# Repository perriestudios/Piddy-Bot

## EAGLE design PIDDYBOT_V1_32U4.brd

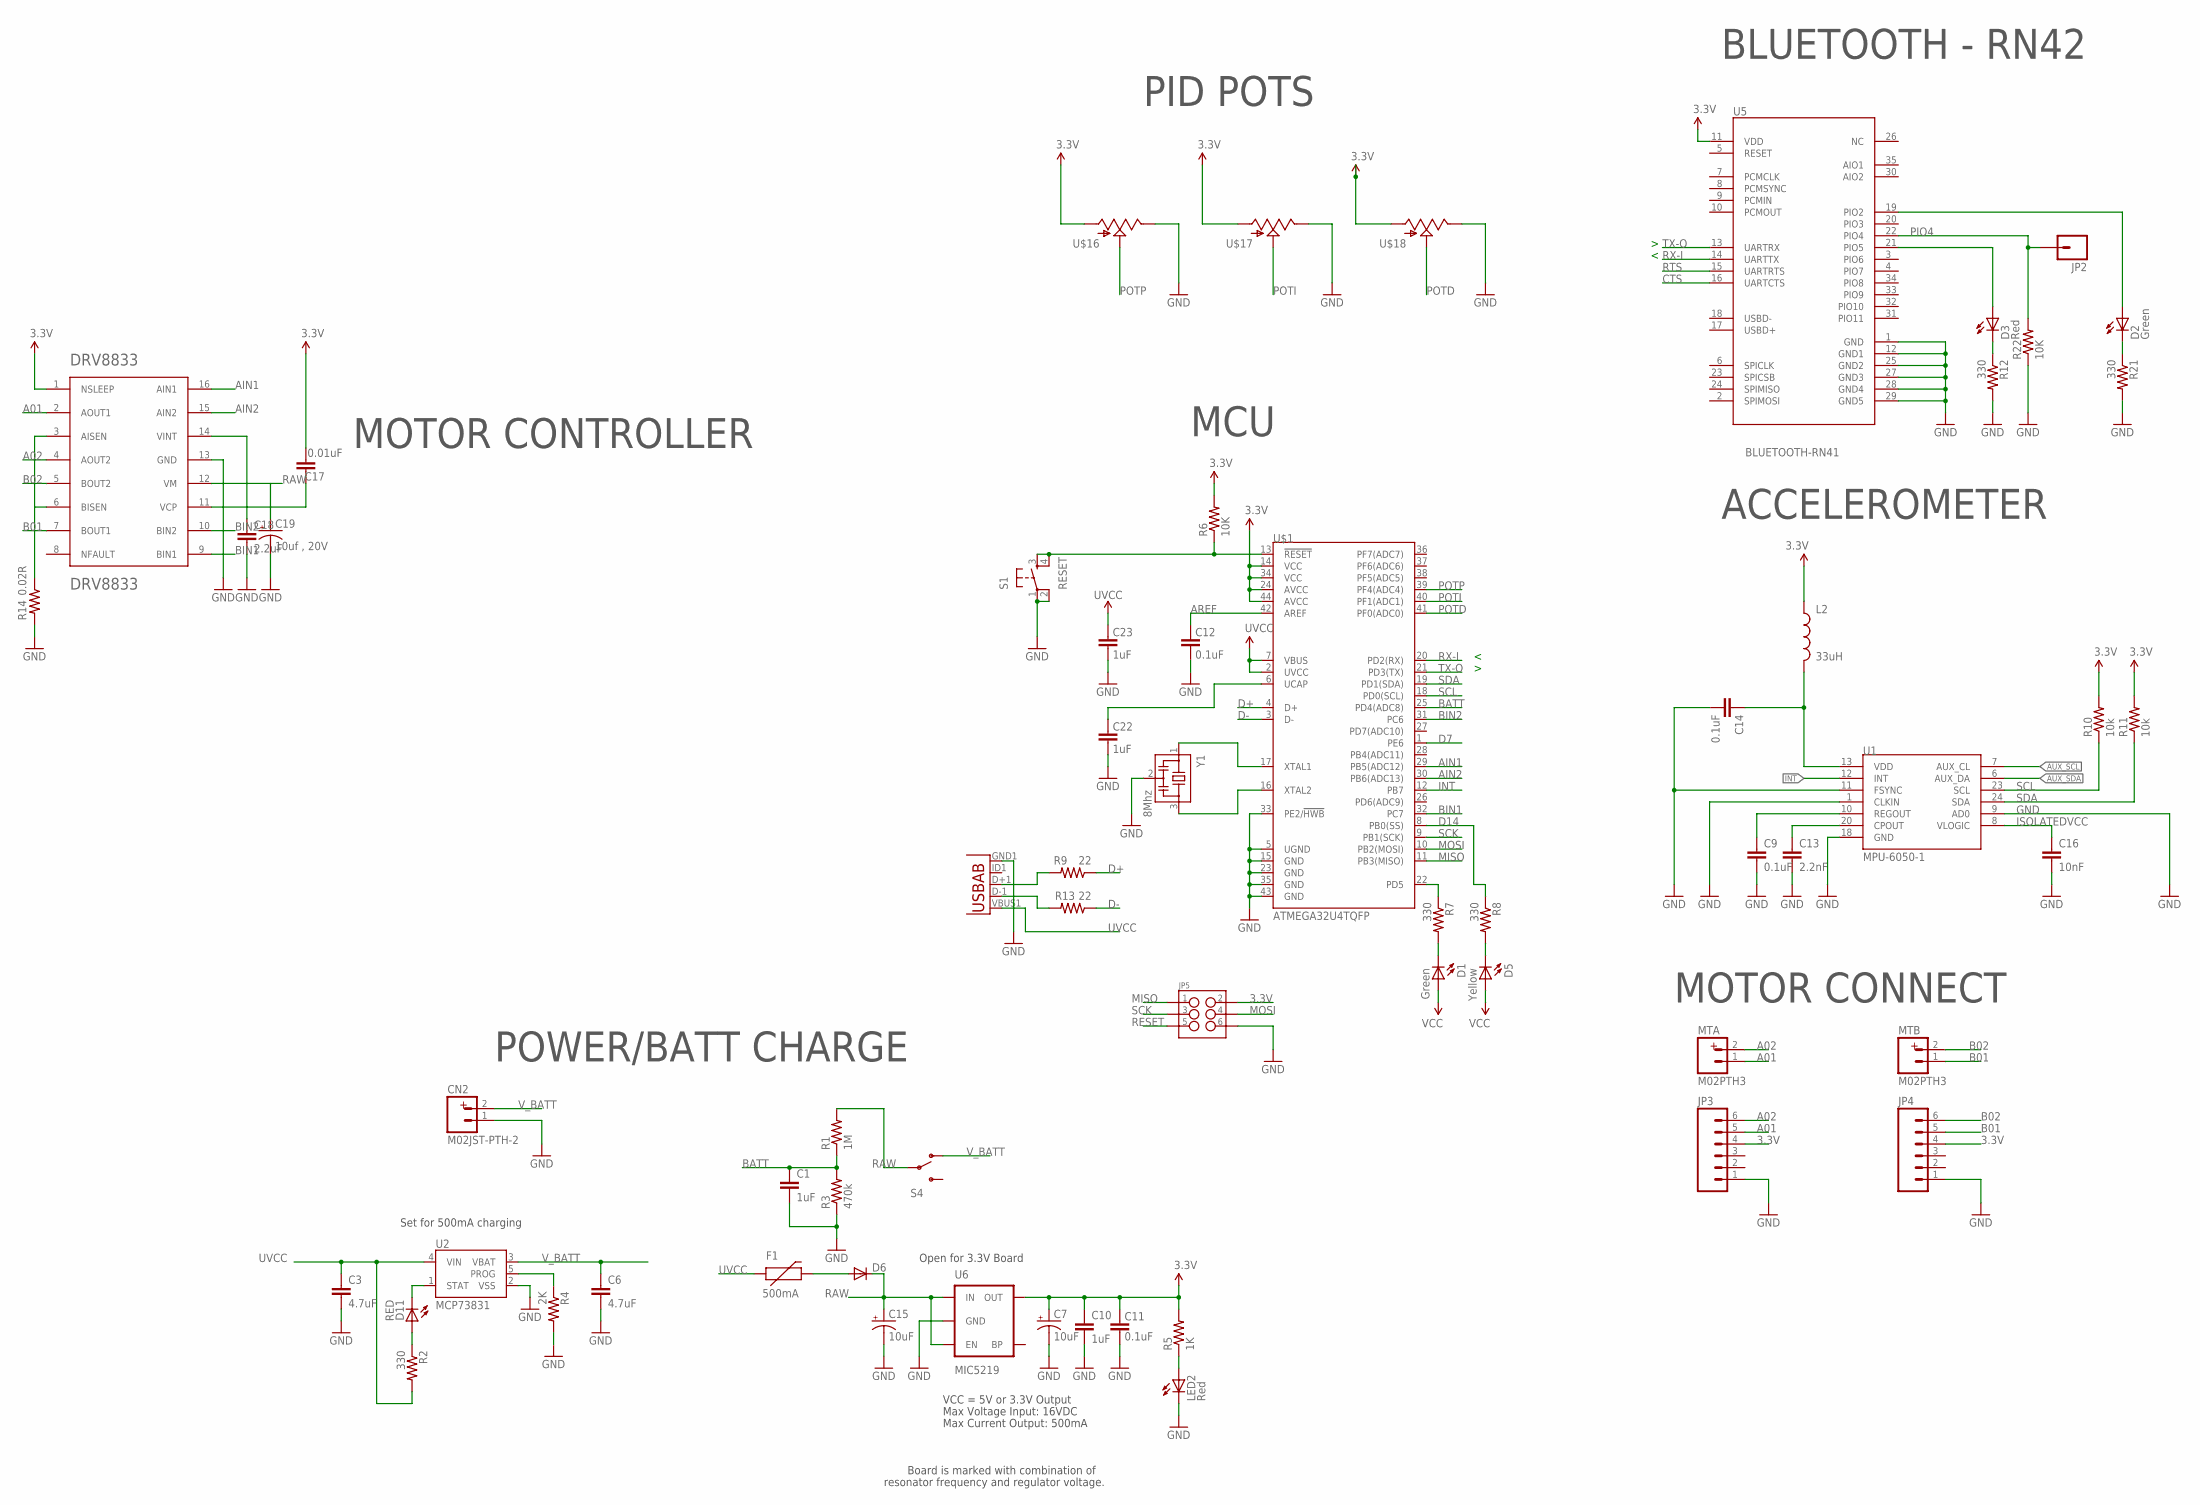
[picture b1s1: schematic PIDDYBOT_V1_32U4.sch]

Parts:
C1, C10, C22, C23: 1uF; 0603-CAP
C3, C6: 4.7uF; 0603-CAP
C7, C15: 10uF; EIA3216
C9, C11, C12, C14: 0.1uF; 0603-CAP
C13: 2.2nF; 0603-CAP
C16: 10nF; 0603-CAP
C17: 0.01uF; 0603-CAP
C18: 2.2uF; 0603-CAP
C19: 10uf , 20V; EIA3528
CN2: M02JST-PTH-2; JST-2-PTH
D1, D2: Green; LED-0603
D3: Red; LED-0603
D5: Yellow; LED-0603
D6: DIODESOD; SOD-323
D11: RED; LED-0603
DRV8833PWP1: DRV8833; SOP65P640X120-17N
F1: 500mA; PTC-1206
JP2: M01SMDNS; 1X01NS
JP3, JP4: M06SMD-1MM; 1X06-1MM
JP5: M03X2NO_SILK; 2X3-NS
L2: 33uH; C0402
LED2: Red; LED-0603
MTA: M02PTH3; 1X02_LONGPADS
MTB: M02PTH3; 1X02_LONGPADS
R1: 1M; 0603-RES
R2, R7, R8, R12, R21: 330; 0603-RES
R3: 470k; 0603-RES
R4: 2K; 0603-RES
R5: 1K; 0603-RES
R6, R22: 10K; 0603-RES
R9, R13: 22; 0603-RES
R10, R11: 10k; 0603-RES
R14: 0.02R; 0603-RES
S1: RESET; TACTILE_SWITCH_SMD
S4: SWITCH-SPDTPTH; SWITCH-SPDT
U1: MPU-6050-1; QFN-24-4MM2
U2: MCP73831; SOT23-5
U5: BLUETOOTH-RN41; RN41
U6: MIC5219; SOT23-5
U$1: ATMEGA32U4TQFP; SPARKFUN-DIGITALIC_TQFP44
U$16, U$17, U$18: POT; ALPS_POT
X2: USB-ABIN&OUT; USB-AB-MICRO-SMD-V03-IN&OUT
Y1: 8Mhz; CSTCR6M

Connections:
3.3V: C7.A (+), C10.1, C11.2, C17.2, D1.A, D5.A, DRV8833PWP1.1 (NSLEEP), JP3.4, JP4.4, JP5.2, L2.1, R5.2, R6.2, R10.2, R11.2, U5.11 (VDD), U6.5 (OUT), U$1.14 (VCC), U$1.24 (AVCC), U$1.34 (VCC), U$1.44 (AVCC), U$16.P$3 (A), U$17.P$3 (A), U$18.P$3 (A)
A01: DRV8833PWP1.2 (AOUT1), JP3.5, MTA.1
A02: DRV8833PWP1.4 (AOUT2), JP3.6, MTA.2
AIN1: DRV8833PWP1.16 (AIN1), U$1.29 (PB5(ADC12))
AIN2: DRV8833PWP1.15 (AIN2), U$1.30 (PB6(ADC13))
AREF: C12.2, U$1.42 (AREF)
AUX_SCL: U1.7 (AUX_CL)
AUX_SDA: U1.6 (AUX_DA)
B01: DRV8833PWP1.7 (BOUT1), JP4.5, MTB.1
B02: DRV8833PWP1.5 (BOUT2), JP4.6, MTB.2
BATT: C1.1, R1.1, R3.2, U$1.25 (PD4(ADC8))
BIN1: DRV8833PWP1.9 (BIN1), U$1.32 (PC7)
BIN2: DRV8833PWP1.10 (BIN2), U$1.31 (PC6)
CTS: U5.16 (UARTCTS)
D1: D3.C, R12.1
D2: D2.C, R21.1
D7: U$1.1 (PE6)
D14: R8.1, U$1.8 (PB0(SS))
D+: R9.1, U$1.4 (D+)
D-: R13.1, U$1.3 (D-)
GND: C1.2, C3.2, C6.2, C7.C (-), C9.2, C10.2, C11.1, C12.1, C13.2, C14.2, C15.C (-), C16.2, C18.2, C19.C (-), C22.1, C23.1, CN2.1, DRV8833PWP1.13 (GND), JP3.1, JP4.1, JP5.6, LED2.C, R3.1, R4.2, R12.2, R14.2, R21.2, R22.1, S1.1, S1.2, U1.1 (CLKIN), U1.9 (AD0), U1.11 (FSYNC), U1.18 (GND), U2.2 (VSS), U5.1 (GND), U5.12 (GND1), U5.25 (GND2), U5.27 (GND3), U5.28 (GND4), U5.29 (GND5), U6.2 (GND), U$1.5 (UGND), U$1.15 (GND), U$1.23 (GND), U$1.33 (PE2/!HWB), U$1.35 (GND), U$1.43 (GND), U$16.P$1 (E), U$17.P$1 (E), U$18.P$1 (E), X2.GND1 (GND), Y1.2
INT: U1.12 (INT), U$1.12 (PB7)
ISOLATEDVCC: C14.1, C16.1, L2.2, U1.8 (VLOGIC), U1.13 (VDD)
MISO: JP5.1, U$1.11 (PB3(MISO))
MOSI: JP5.4, U$1.10 (PB2(MOSI))
unnamed: U$1.17 (XTAL1), Y1.1
unnamed: U$1.16 (XTAL2), Y1.3
unnamed: D6.2 (A), F1.2
unnamed: C13.1, U1.20 (CPOUT)
unnamed: C9.1, U1.10 (REGOUT)
unnamed: D3.A, U5.21 (PIO5)
unnamed: D2.A, U5.19 (PIO2)
unnamed: D11.A, R2.1
unnamed: C22.2, U$1.6 (UCAP)
unnamed: R13.2, X2.D-1 (D-)
unnamed: R9.2, X2.D+1 (D+)
unnamed: C17.1, DRV8833PWP1.11 (VCP)
unnamed: D5.C, R8.2
unnamed: D1.C, R7.2
unnamed: DRV8833PWP1.3 (AISEN), DRV8833PWP1.6 (BISEN), R14.1
unnamed: C18.1, DRV8833PWP1.14 (VINT)
unnamed: LED2.A, R5.1
PIO4: JP2.1, R22.2, U5.22 (PIO4)
POTD: U$1.41 (PF0(ADC0)), U$18.P$2 (S)
POTI: U$1.40 (PF1(ADC1)), U$17.P$2 (S)
POTP: U$1.39 (PF4(ADC4)), U$16.P$2 (S)
PROG: R4.1, U2.5 (PROG)
RAW: C15.A (+), C19.A (+), D6.1 (C), DRV8833PWP1.12 (VM), R1.2, S4.2, U6.1 (IN), U6.3 (EN)
RESET: JP5.5, R6.1, S1.3, S1.4, U$1.13 (!RESET)
RTS: U5.15 (UARTRTS)
RX-I: U5.14 (UARTTX), U$1.20 (PD2(RX))
SCK: JP5.3, U$1.9 (PB1(SCK))
SCL: R10.1, U1.23 (SCL), U$1.18 (PD0(SCL))
SDA: R11.1, U1.24 (SDA), U$1.19 (PD1(SDA))
STAT: D11.C, U2.1 (STAT)
TX-O: U5.13 (UARTRX), U$1.21 (PD3(TX))
TXLED: R7.1, U$1.22 (PD5)
UVCC: C3.1, C23.2, F1.1, R2.2, U2.4 (VIN), U$1.2 (UVCC), U$1.7 (VBUS), X2.VBUS1 (VBUS)
V_BATT: C6.1, CN2.2, S4.1 (O), U2.3 (VBAT)

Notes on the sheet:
Set for 500mA charging
Max Voltage Input: 16VDC
Max Current Output: 500mA
Board is marked with combination of
resonator frequency and regulator voltage.
VCC = 5V or 3.3V Output
Open for 3.3V Board
MOTOR CONTROLLER
MCU
PID POTS
BLUETOOTH - RN42
ACCELEROMETER
MOTOR CONNECT
POWER/BATT CHARGE

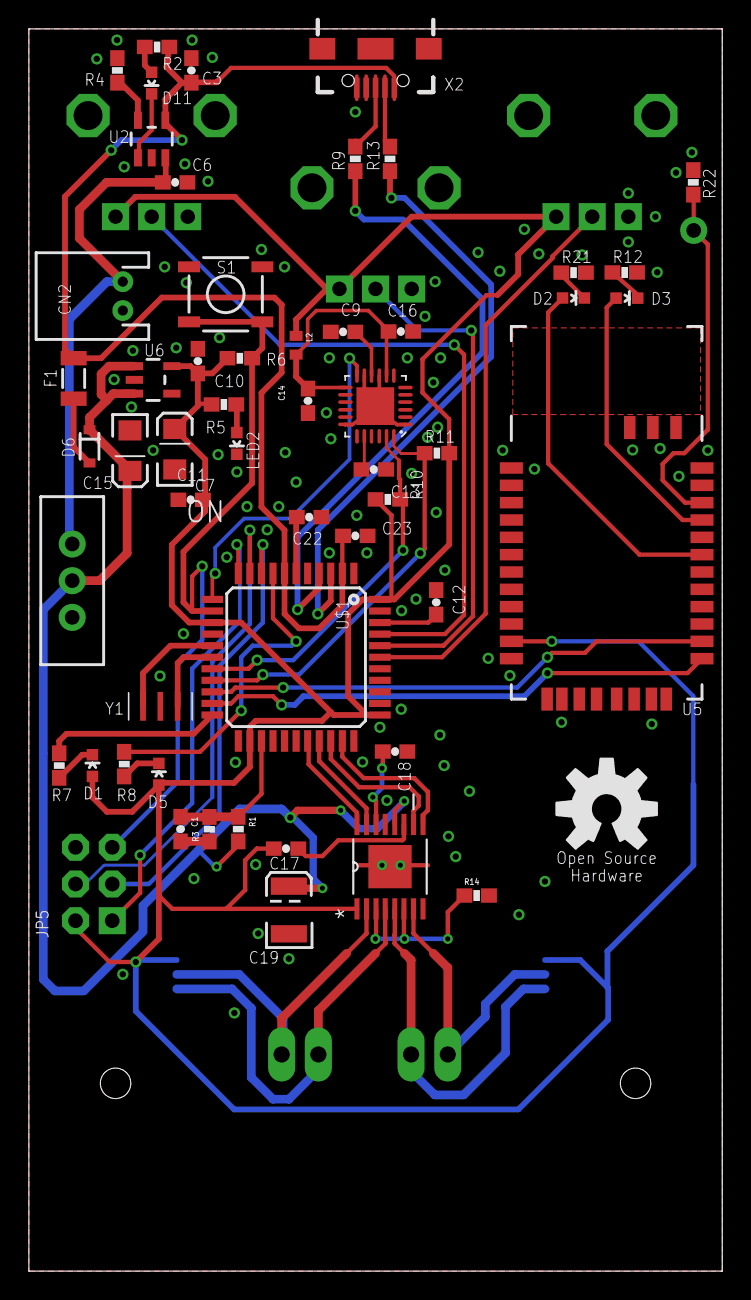
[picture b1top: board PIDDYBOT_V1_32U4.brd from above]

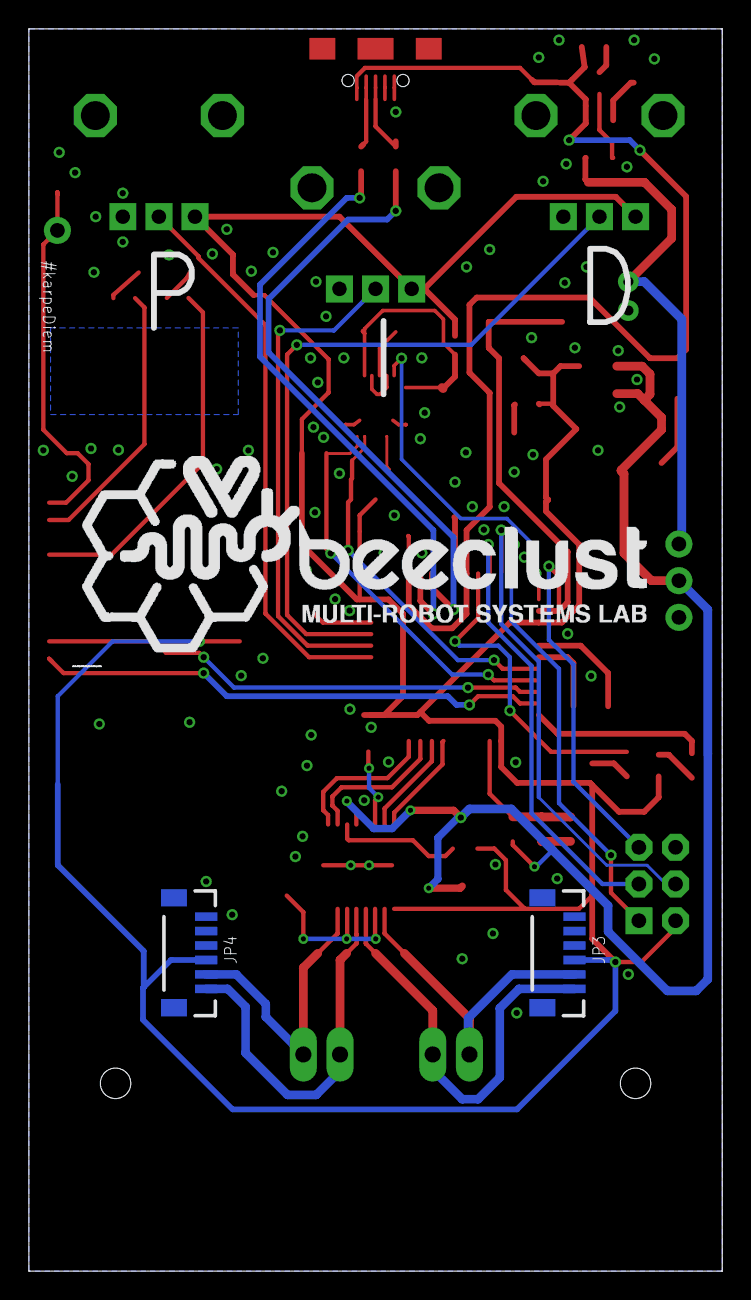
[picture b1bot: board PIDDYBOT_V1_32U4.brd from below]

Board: 2 copper layers, 48.0 x 86.0 mm, 64 parts (6 on the bottom side), 54 nets.

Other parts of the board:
U$2: LOGO-L
U$3: OSHW-LOGO-L

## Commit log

2020-11-17 Added the files
2020-11-17 Removed junk file

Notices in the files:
parts and their libraries:
SparkFun-Connectors: Licensing: CC v3.0 Share-Alike You are welcome to use this library for commercial purposes.
SparkFun-Aesthetics: Licensing: Creative Commons ShareAlike 4.0 International - https://creativecommons.org/licenses/by-sa/4.0
